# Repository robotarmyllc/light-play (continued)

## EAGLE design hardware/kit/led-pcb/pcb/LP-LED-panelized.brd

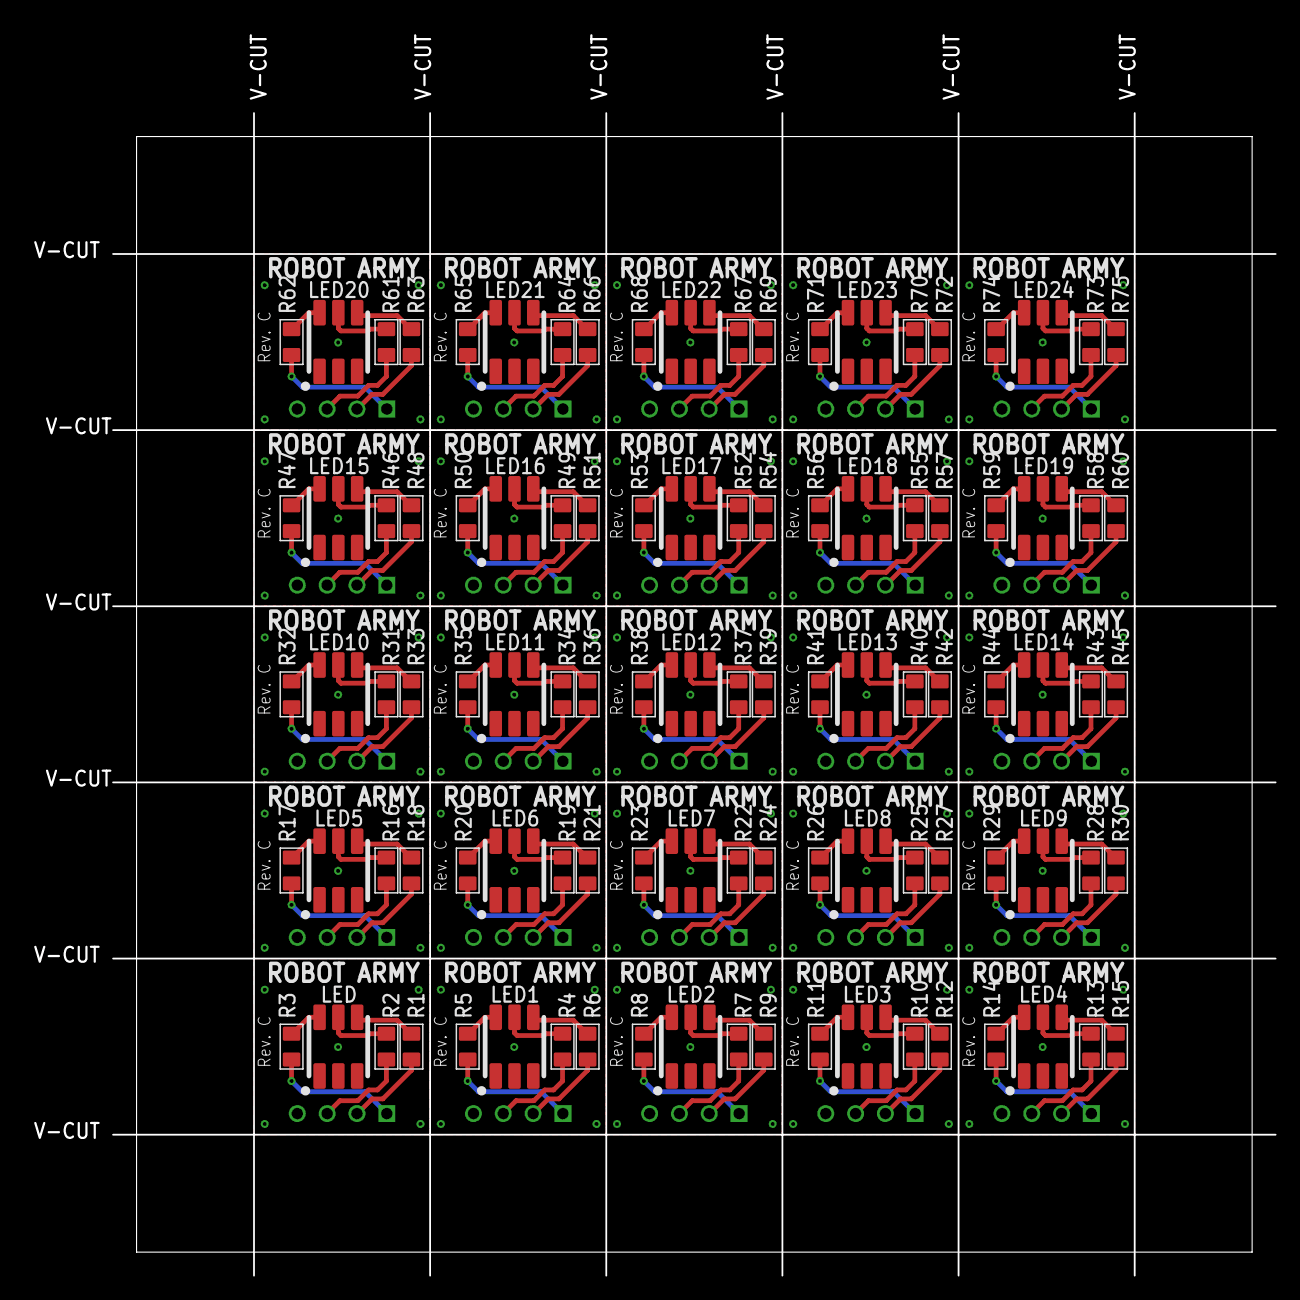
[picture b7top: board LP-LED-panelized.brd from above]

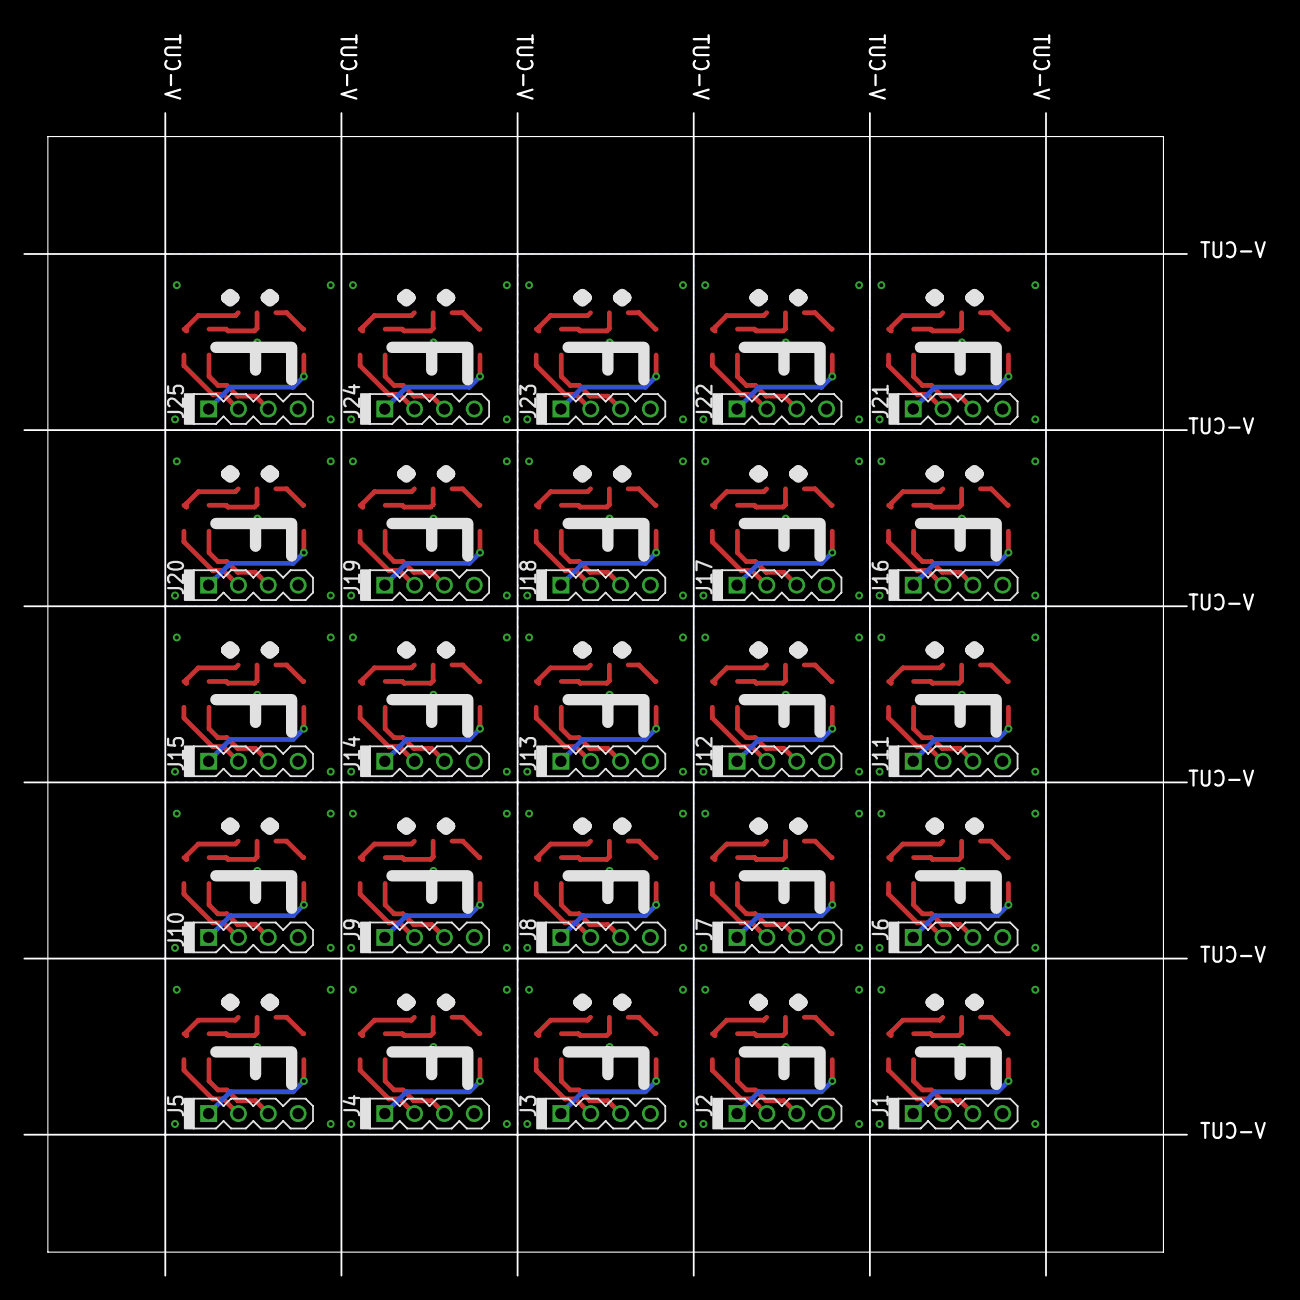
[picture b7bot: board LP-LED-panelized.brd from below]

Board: 2 copper layers, 106.6 x 106.6 mm, 125 parts (25 on the bottom side), 175 nets.

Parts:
J1, J2, J3, J4, J5, J6, J7, J8, J9, J10, J11, J12, J13, J14, J15, J16, J17, J18, J19, J20, J21, J22, J23, J24, J25: MA04-1
LED, LED1, LED2, LED3, LED4, LED5, LED6, LED7, LED8, LED9, LED10, LED11, LED12, LED13, LED14, LED15, LED16, LED17, LED18, LED19, LED20, LED21, LED22, LED23, LED24: PLCC-6
R1, R3, R5, R6, R8, R9, R11, R12, R14, R15, R17, R18, R20, R21, R23, R24, R26, R27, R29, R30, R32, R33, R35, R36, R38, R39, R41, R42, R44, R45, R47, R48, R50, R51, R53, R54, R56, R57, R59, R60, R62, R63, R65, R66, R68, R69, R71, R72, R74, R75: 133; 0805
R2, R4, R7, R10, R13, R16, R19, R22, R25, R28, R31, R34, R37, R40, R43, R46, R49, R52, R55, R58, R61, R64, R67, R70, R73: 200; 0805

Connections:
COMMON: J1.4, LED.1, LED.2, LED.3
COMMON1: J2.4, LED1.1, LED1.2, LED1.3
COMMON2: J3.4, LED2.1, LED2.2, LED2.3
COMMON3: J4.4, LED3.1, LED3.2, LED3.3
COMMON4: J5.4, LED4.1, LED4.2, LED4.3
COMMON5: J6.4, LED5.1, LED5.2, LED5.3
COMMON6: J7.4, LED6.1, LED6.2, LED6.3
COMMON7: J8.4, LED7.1, LED7.2, LED7.3
COMMON8: J9.4, LED8.1, LED8.2, LED8.3
COMMON9: J10.4, LED9.1, LED9.2, LED9.3
COMMON10: J11.4, LED10.1, LED10.2, LED10.3
COMMON11: J12.4, LED11.1, LED11.2, LED11.3
COMMON12: J13.4, LED12.1, LED12.2, LED12.3
COMMON13: J14.4, LED13.1, LED13.2, LED13.3
COMMON14: J15.4, LED14.1, LED14.2, LED14.3
COMMON15: J16.4, LED15.1, LED15.2, LED15.3
COMMON16: J17.4, LED16.1, LED16.2, LED16.3
COMMON17: J18.4, LED17.1, LED17.2, LED17.3
COMMON18: J19.4, LED18.1, LED18.2, LED18.3
COMMON19: J20.4, LED19.1, LED19.2, LED19.3
COMMON20: J21.4, LED20.1, LED20.2, LED20.3
COMMON21: J22.4, LED21.1, LED21.2, LED21.3
COMMON22: J23.4, LED22.1, LED22.2, LED22.3
COMMON23: J24.4, LED23.1, LED23.2, LED23.3
COMMON24: J25.4, LED24.1, LED24.2, LED24.3
unnamed: LED.4, R1.2
unnamed: J1.3, R2.1
unnamed: LED.6, R3.2
unnamed: LED.5, R2.2
unnamed: J1.2, R1.1
unnamed: J1.1, R3.1
unnamed: LED1.6, R5.2
unnamed: J2.1, R5.1
unnamed: J2.2, R6.1
unnamed: LED1.4, R6.2
unnamed: J2.3, R4.1
unnamed: LED1.5, R4.2
unnamed: LED2.6, R8.2
unnamed: J3.1, R8.1
unnamed: J3.2, R9.1
unnamed: LED2.4, R9.2
unnamed: J3.3, R7.1
unnamed: LED2.5, R7.2
unnamed: LED3.6, R11.2
unnamed: J4.1, R11.1
unnamed: J4.2, R12.1
unnamed: LED3.4, R12.2
unnamed: J4.3, R10.1
unnamed: LED3.5, R10.2
unnamed: LED4.6, R14.2
unnamed: J5.1, R14.1
unnamed: J5.2, R15.1
unnamed: LED4.4, R15.2
unnamed: J5.3, R13.1
unnamed: LED4.5, R13.2
unnamed: LED5.6, R17.2
unnamed: J6.1, R17.1
unnamed: J6.2, R18.1
unnamed: LED5.4, R18.2
unnamed: J6.3, R16.1
unnamed: LED5.5, R16.2
unnamed: LED6.6, R20.2
unnamed: J7.1, R20.1
unnamed: J7.2, R21.1
unnamed: LED6.4, R21.2
unnamed: J7.3, R19.1
unnamed: LED6.5, R19.2
unnamed: LED7.6, R23.2
unnamed: J8.1, R23.1
unnamed: J8.2, R24.1
unnamed: LED7.4, R24.2
unnamed: J8.3, R22.1
unnamed: LED7.5, R22.2
unnamed: LED8.6, R26.2
unnamed: J9.1, R26.1
unnamed: J9.2, R27.1
unnamed: LED8.4, R27.2
unnamed: J9.3, R25.1
unnamed: LED8.5, R25.2
unnamed: LED9.6, R29.2
unnamed: J10.1, R29.1
unnamed: J10.2, R30.1
unnamed: LED9.4, R30.2
unnamed: J10.3, R28.1
unnamed: LED9.5, R28.2
unnamed: LED10.6, R32.2
unnamed: J11.1, R32.1
unnamed: J11.2, R33.1
unnamed: LED10.4, R33.2
unnamed: J11.3, R31.1
unnamed: LED10.5, R31.2
unnamed: LED11.6, R35.2
unnamed: J12.1, R35.1
unnamed: J12.2, R36.1
unnamed: LED11.4, R36.2
unnamed: J12.3, R34.1
unnamed: LED11.5, R34.2
unnamed: LED12.6, R38.2
unnamed: J13.1, R38.1
unnamed: J13.2, R39.1
unnamed: LED12.4, R39.2
unnamed: J13.3, R37.1
unnamed: LED12.5, R37.2
unnamed: LED13.6, R41.2
unnamed: J14.1, R41.1
unnamed: J14.2, R42.1
unnamed: LED13.4, R42.2
unnamed: J14.3, R40.1
unnamed: LED13.5, R40.2
unnamed: LED14.6, R44.2
unnamed: J15.1, R44.1
unnamed: J15.2, R45.1
unnamed: LED14.4, R45.2
unnamed: J15.3, R43.1
unnamed: LED14.5, R43.2
unnamed: LED15.6, R47.2
unnamed: J16.1, R47.1
unnamed: J16.2, R48.1
unnamed: LED15.4, R48.2
unnamed: J16.3, R46.1
unnamed: LED15.5, R46.2
unnamed: LED16.6, R50.2
unnamed: J17.1, R50.1
unnamed: J17.2, R51.1
unnamed: LED16.4, R51.2
unnamed: J17.3, R49.1
unnamed: LED16.5, R49.2
unnamed: LED17.6, R53.2
unnamed: J18.1, R53.1
unnamed: J18.2, R54.1
unnamed: LED17.4, R54.2
unnamed: J18.3, R52.1
unnamed: LED17.5, R52.2
unnamed: LED18.6, R56.2
unnamed: J19.1, R56.1
unnamed: J19.2, R57.1
unnamed: LED18.4, R57.2
unnamed: J19.3, R55.1
unnamed: LED18.5, R55.2
unnamed: LED19.6, R59.2
unnamed: J20.1, R59.1
unnamed: J20.2, R60.1
unnamed: LED19.4, R60.2
unnamed: J20.3, R58.1
unnamed: LED19.5, R58.2
unnamed: LED20.6, R62.2
unnamed: J21.1, R62.1
unnamed: J21.2, R63.1
unnamed: LED20.4, R63.2
unnamed: J21.3, R61.1
unnamed: LED20.5, R61.2
unnamed: LED21.6, R65.2
unnamed: J22.1, R65.1
unnamed: J22.2, R66.1
unnamed: LED21.4, R66.2
unnamed: J22.3, R64.1
unnamed: LED21.5, R64.2
unnamed: LED22.6, R68.2
unnamed: J23.1, R68.1
unnamed: J23.2, R69.1
unnamed: LED22.4, R69.2
unnamed: J23.3, R67.1
unnamed: LED22.5, R67.2
unnamed: LED23.6, R71.2
unnamed: J24.1, R71.1
unnamed: J24.2, R72.1
unnamed: LED23.4, R72.2
unnamed: J24.3, R70.1
unnamed: LED23.5, R70.2
unnamed: LED24.6, R74.2
unnamed: J25.1, R74.1
unnamed: J25.2, R75.1
unnamed: LED24.4, R75.2
unnamed: J25.3, R73.1
unnamed: LED24.5, R73.2

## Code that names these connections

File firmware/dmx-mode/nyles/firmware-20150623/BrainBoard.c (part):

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
    // Construct channel
    dmx_chan =   ~PINC & 0x0F;
    // dmx_chan |= (~PINC & 0x20) << 3;     // PC5 is bit 8 - NOW IT IS ACCEL CONT ENABLE
    dmx_chan |= (~PIND & 0x04) << 4;     // PD2 is bit 7
    dmx_chan |= (~PIND & 0x10) << 2;     // PD4 is bit 6   BUG FIX 20150708
    dmx_chan |= (~PIND & 0x80) >> 3;     // PD7 is bit 5
    //
    // Channel 0 is a mode byte, not data - so add 1
    // dmx_chan = (dmx_chan * 6) + 1;
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
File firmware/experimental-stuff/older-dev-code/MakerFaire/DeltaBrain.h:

#ifndef DELTA_BRAIN_H
#define DELTA_BRAIN_H

class DeltaBrain {
   
   public:
     DeltaBrain();
     void begin();
     int getDIP();
     void enableMotors();
     void disableMotors();
     void setLED( int r, int g, int b);
     void flashLED( int count, int r, int g, int b );
     
   private:
     const static int LED_R = 3;
     const static int LED_G = 5;
     const static int LED_B = 6;
     
     const static int MOTOR_EN = 8;
};


#endif

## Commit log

2022-09-13 rev-a pcb
2022-09-13 Brain Rev B
2022-09-13 rev-c board
2022-09-13 rev-d board
2022-09-13 rev-e board
2022-09-13 added brain test fixture
2022-09-13 DMX A-type board - rev a
2022-09-13 DMX a-type board rev B
2022-09-13 DMX type-B board. Rev. A
2022-09-13 hardware kit things
2022-09-13 led pcb rev-a
2022-09-13 rev-b pcb
2022-09-13 rev-c pcb
2022-09-13 DMX cat5 connector board
2022-09-13 DMX cat5 board rev-b
2022-09-13 random mechanical stuff
2022-09-13 refactor and merge repositories
2022-09-13 various software stuff
2022-09-13 media stuff
2022-09-13 qlc files for dmx control
2022-09-13 Added kit intructions.
